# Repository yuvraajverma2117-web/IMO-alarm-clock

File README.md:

# IMO GENIUS ALARM

A hardware alarm-clock project by **@YuviVerma**. The Stardance project describes the goal as setting a stopwatch or alarm for a long maths session.

## Contents

- `imo-genius-alarm/Journal.md` — dated, source-grounded record of the three devlogs and the files gathered.
- `imo-genius-alarm/images/devlogs/` — four WebP images downloaded from the three Stardance devlogs.
- `imo-genius-alarm/hardware/kicad/` — KiCad project, PCB, schematic, and exported component CSV.
- `imo-genius-alarm/hardware/3d-models/` — the KiCad STEP assembly export and a TFT display STEP model.
- `imo-genius-alarm/hardware/fusion/` — a local Fusion 360 `.f3d` file and its PNG preview.

## File notes

The KiCad CSV lists nine push switches, nine 1N4148 diodes, a buzzer, and a XIAO ESP32-C3. Its U1 designation says `XIAO-ESP32-C3-SMD`, while its footprint column says `XIAO-ESP32-C3-DIP`; verify this mismatch before ordering or manufacturing. The PCB also contains absolute 3D-model paths into the original Mac Downloads folder and `${AMZPATH}` references, so its 3D view may need repair after cloning.

The Fusion preview depicts a PCB assembly, not a clock enclosure. The KiCad STEP file identifies itself as a KiCad electronic-assembly export. No separate enclosure CAD source or firmware source was found among the matching project files. The newest devlog says enclosure CAD work had started, so the included assembly should not be presented as a finished alarm-clock case or tested product.

No license was selected or added. The original KiCad preferences, temporary files, and duplicate copies were left out. The duplicate KiCad board and schematic found in `IMO Alarm Clock 2` were byte-identical to the selected project files.

## Stardance source

- [IMO GENIUS ALARM project](https://stardance.hackclub.com/projects/59242)
- [2026-10-29 devlog — alarm-clock CAD started](https://stardance.hackclub.com/projects/59242/devlogs/70197)
- [2026-10-26 devlog — PCB and schematic](https://stardance.hackclub.com/projects/59242/devlogs/69298)
- [2026-09-11 devlog — PCB tutorial and footprint work](https://stardance.hackclub.com/projects/59242/devlogs/55090)

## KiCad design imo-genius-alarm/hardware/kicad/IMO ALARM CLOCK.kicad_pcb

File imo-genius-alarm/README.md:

# IMO GENIUS ALARM

A hardware alarm-clock project by **@YuviVerma**. The Stardance project describes the goal as setting a stopwatch or alarm for a long maths session.

## Contents

- `Journal.md` — dated, source-grounded record of the three devlogs and the files gathered.
- `images/devlogs/` — four WebP images downloaded from the three Stardance devlogs.
- `hardware/kicad/` — KiCad project, PCB, schematic, and exported component CSV.
- `hardware/3d-models/` — the KiCad STEP assembly export and a TFT display STEP model.
- `hardware/fusion/` — a local Fusion 360 `.f3d` file and its PNG preview.

## File notes

The KiCad CSV lists nine push switches, nine 1N4148 diodes, a buzzer, and a XIAO ESP32-C3. Its U1 designation says `XIAO-ESP32-C3-SMD`, while its footprint column says `XIAO-ESP32-C3-DIP`; verify this mismatch before ordering or manufacturing. The PCB also contains absolute 3D-model paths into the original Mac Downloads folder and `${AMZPATH}` references, so its 3D view may need repair after cloning.

The Fusion preview depicts a PCB assembly, not a clock enclosure. The KiCad STEP file identifies itself as a KiCad electronic-assembly export. No separate enclosure CAD source or firmware source was found among the matching project files. The newest devlog says enclosure CAD work had started, so the included assembly should not be presented as a finished alarm-clock case or tested product.

No license was selected or added. The original KiCad preferences, temporary files, and duplicate copies were left out. The duplicate KiCad board and schematic found in `IMO Alarm Clock 2` were byte-identical to the selected project files.

## Stardance source

- [IMO GENIUS ALARM project](https://stardance.hackclub.com/projects/59242)
- [2026-10-29 devlog — alarm-clock CAD started](https://stardance.hackclub.com/projects/59242/devlogs/70197)
- [2026-10-26 devlog — PCB and schematic](https://stardance.hackclub.com/projects/59242/devlogs/69298)
- [2026-09-11 devlog — PCB tutorial and footprint work](https://stardance.hackclub.com/projects/59242/devlogs/55090)

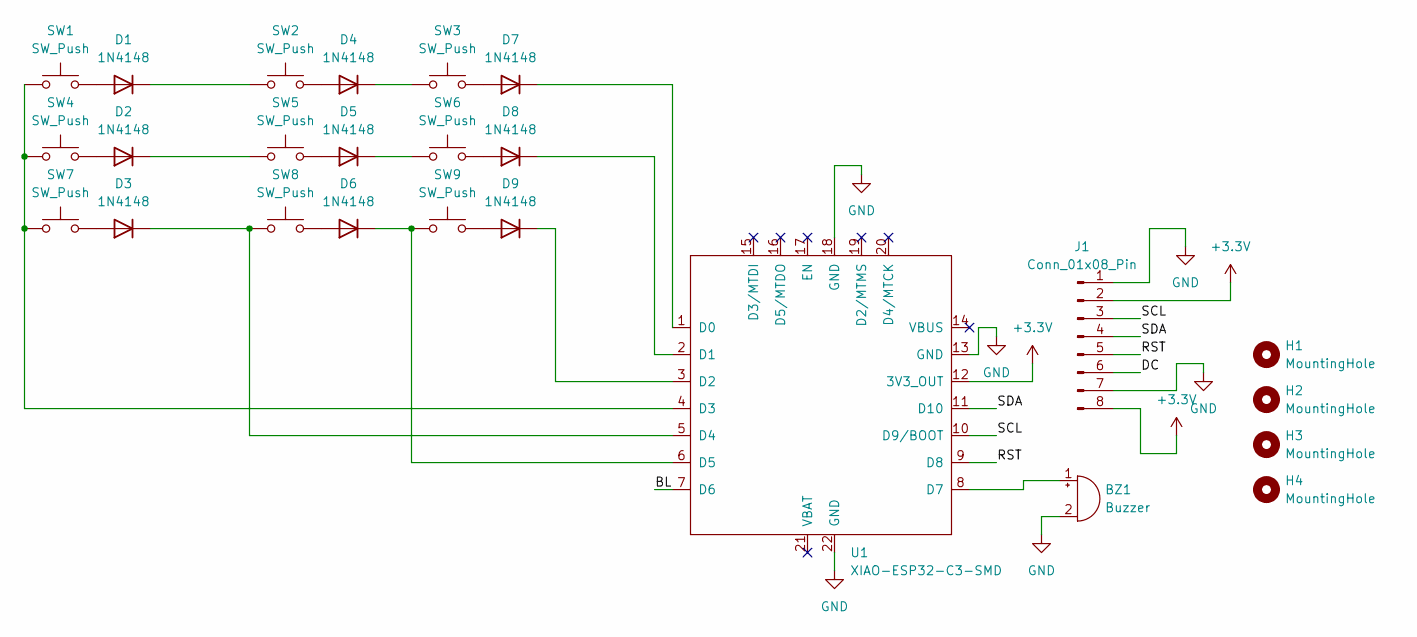
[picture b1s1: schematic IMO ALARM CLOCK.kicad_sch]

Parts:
BZ1: Buzzer; Buzzer_12x9.5RM7.6
D1, D2, D3, D4, D5, D6, D7, D8, D9: 1N4148; D_DO-35_SOD27_P7.62mm_Horizontal
H1, H2, H3, H4: MountingHole; MountingHole_3.2mm_M3
J1: Conn_01x08_Pin; PinSocket_1x08_P2.54mm_Vertical
SW1, SW2, SW3, SW4, SW5, SW6, SW7, SW8, SW9: SW_Push; SW_Cherry_MX_1.00u_PCB
U1: XIAO-ESP32-C3-SMD; XIAO-ESP32-C3-DIP

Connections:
+3.3V: J1.2, J1.8, U1.12 (3V3_OUT)
/BL: U1.7 (D6)
/DC: J1.6
/RST: J1.5, U1.9 (D8)
/SCL: J1.3, U1.10 (D9/BOOT)
/SDA: J1.4, U1.11 (D10)
GND: BZ1.2 (-), J1.1, J1.7, U1.13 (GND), U1.18 (GND), U1.22 (GND)
unnamed: BZ1.1 (+), U1.8 (D7)
unnamed: D1.2 (A), SW1.2
unnamed: D1.1 (K), SW2.1
unnamed: D2.2 (A), SW4.2
unnamed: D2.1 (K), SW5.1
unnamed: D3.2 (A), SW7.2
unnamed: D3.1 (K), SW8.1, U1.5 (D4)
unnamed: D4.2 (A), SW2.2
unnamed: D4.1 (K), SW3.1
unnamed: D5.2 (A), SW5.2
unnamed: D5.1 (K), SW6.1
unnamed: D6.2 (A), SW8.2
unnamed: D6.1 (K), SW9.1, U1.6 (D5)
unnamed: D7.2 (A), SW3.2
unnamed: D7.1 (K), U1.1 (D0)
unnamed: D8.2 (A), SW6.2
unnamed: D8.1 (K), U1.2 (D1)
unnamed: D9.2 (A), SW9.2
unnamed: D9.1 (K), U1.3 (D2)
unnamed: SW1.1, SW4.1, SW7.1, U1.4 (D3)

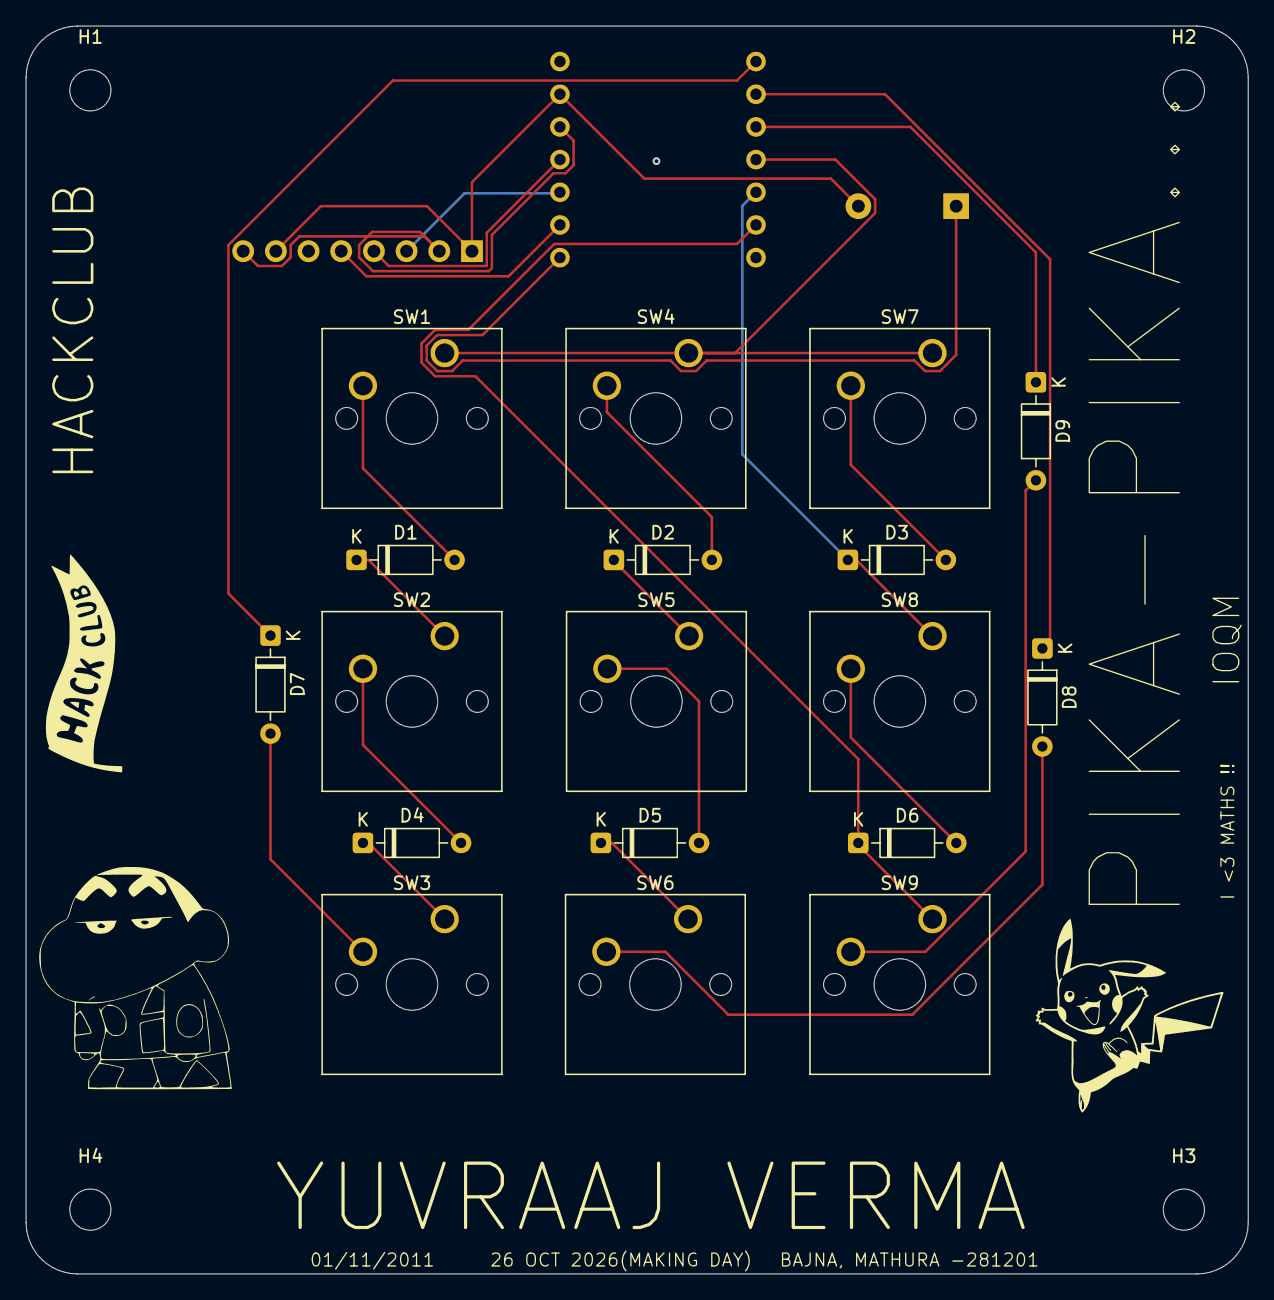
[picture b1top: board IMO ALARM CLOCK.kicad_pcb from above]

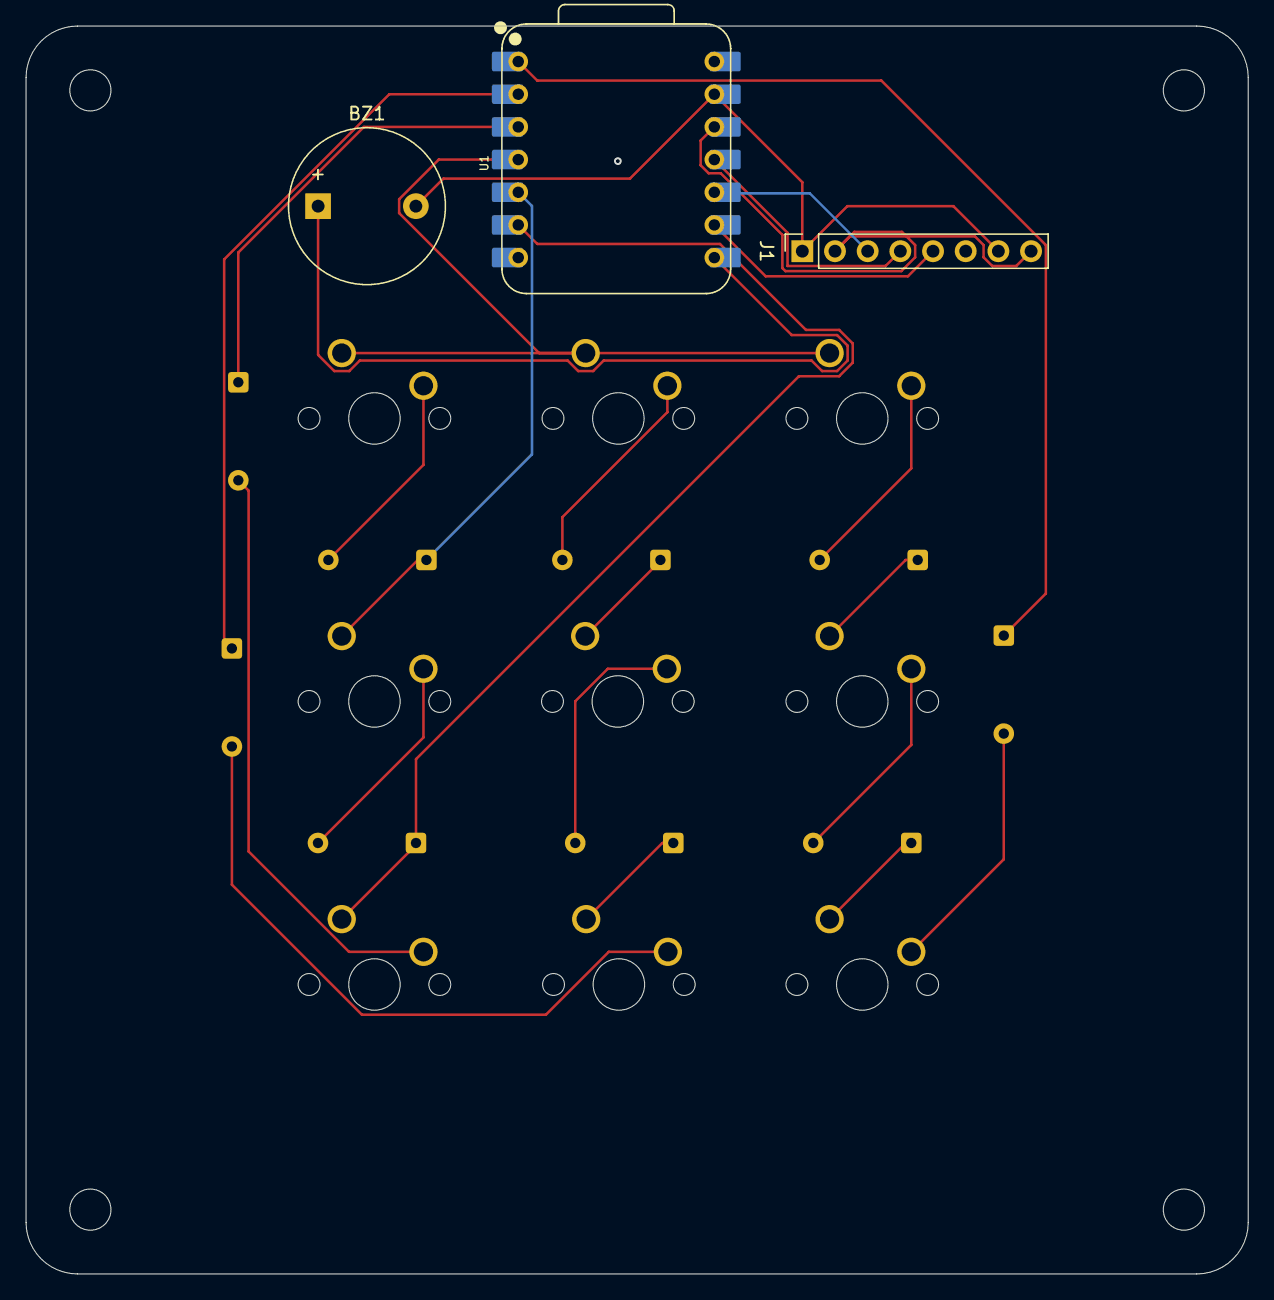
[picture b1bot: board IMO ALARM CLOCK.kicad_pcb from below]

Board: 2 copper layers, 95.0 x 97.0 mm, 25 parts (3 on the bottom side), 25 nets.
